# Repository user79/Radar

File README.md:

# Radar
This is a Frequency Modulated Continuous Wave (FMCW) ground penetrating radar (GPR) project aimed toward detection of land mines for humanitarian de-mining. It is based loosely on the online resources from MIT and U.C.Davis, as well as the presentation by Ferrara/Chizh/Pietrelli 2017.
* https://ocw.mit.edu/courses/res-ll-003-build-a-small-radar-system-capable-of-sensing-range-doppler-and-synthetic-aperture-radar-imaging-january-iap-2011/
* http://gpradar.eu/onewebmedia/TU1208_GPRforeducationaluse_November2017_FerraraChizhPietrelli.pdf
* https://github.com/ucdart/UCD-EEC134/
* http://dart.ece.ucdavis.edu/education/eec134.html
* http://dart.ece.ucdavis.edu/education/files/eec134-2017-2018/Team_DiodeHard3/AN_Yharo_Torres.pdf
* http://dart.ece.ucdavis.edu/education/files/eec134-2017-2018/Team_DeepSpaceAntenna/Team_DeepSpace_Antenna_Report.pdf

Here I have posted the circuit design, Eagle CAD schematic, and board layout for revision 1.

Unfortunately, in initial testing of this board with a sawtooth voltage input to produce a standard frequency sweep (and subsequent testing with discrete DC voltage inputs), the output voltage seems to be fluctuating according to some other pattern, not related to reflectors placed at varying distances from the antennas.  My initial guess is that there is a reflection (or set of reflections) from the board itself that is causing the mixing pattern, that is overshadowing any additional reflection mixing from the receive antenna.  There may be some coupling from the traces of the PCB.  The projects above used shielded coax cable to connect the various parts, and now I can see why.

Next, in summer 2023, I did some hardware testing with a different mixer (but using the same VCO from the original board). I was able to see radar action in tracking a person walking in a hallway, as shown. However, I was hitting some fundamental limits in resolution due to sampling rate and wavelength and other issues, as described in the "GPR progress summer2023.pdf" document.

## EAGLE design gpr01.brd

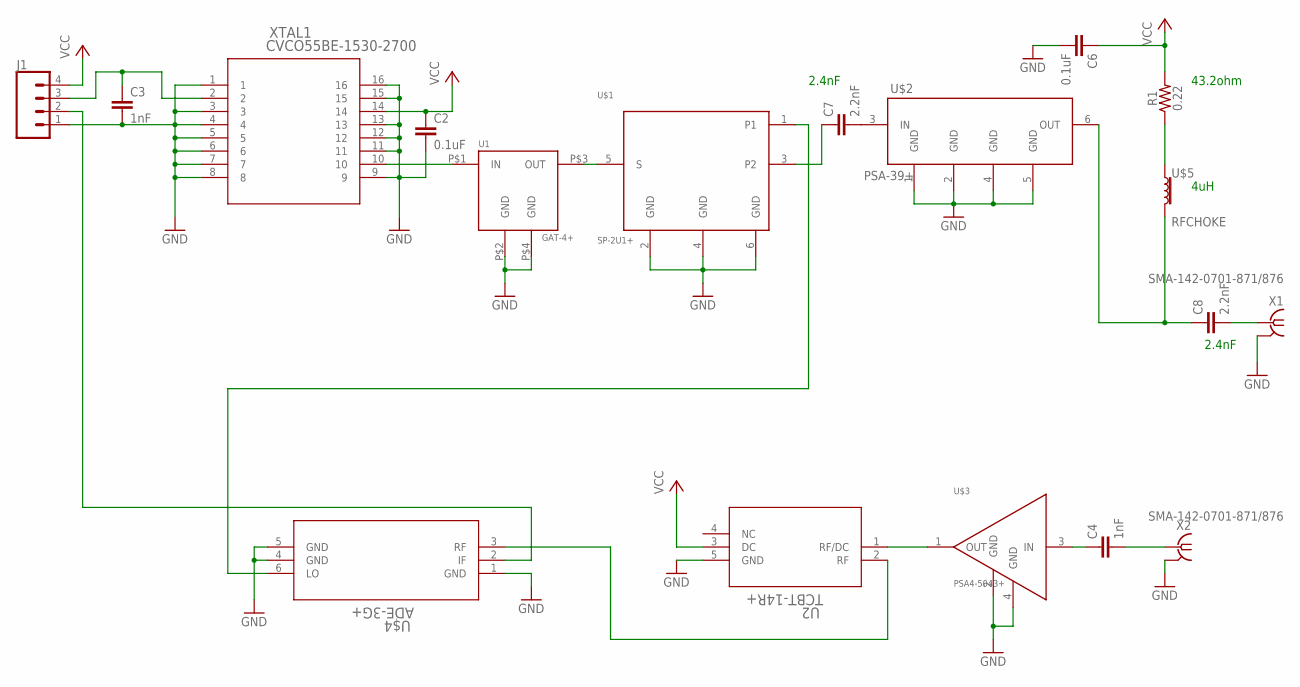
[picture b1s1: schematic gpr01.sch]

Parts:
C2, C6: 0.1uF; 0402
C3, C4: 1nF; 0603
C7, C8: 2.2nF; 0603
J1: CONN_04POLAR; MOLEX-1X4
R1: 0.22; 0805
U1: GAT-4+
U2: TCBT-14R+; GU1414-2_MNC
U$1: SP-2U1+; SOT23-6
U$2: PSA-39+; SOT363_PHILIPS
U$3: PSA4-5043+; SOT343
U$4: ADE-3G+; CD542_MNC
U$5: RFCHOKE; 1210
X1, X2: SMA-142-0701-871/876; J502-ND-142-0701-871/876
XTAL1: CVCO55BE-1530-2700; CVCO55BE-1530-2700_CRX

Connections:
GND: C2.2, C3.2, C6.2, J1.1, U1.P$2 (GND), U1.P$4 (GND), U2.5 (GND), U$1.2 (GND), U$1.4 (GND), U$1.6 (GND), U$2.1 (GND), U$2.2 (GND), U$2.4 (GND), U$2.5 (GND), U$3.2 (GND), U$3.4 (GND), U$4.1 (GND), U$4.4 (GND), U$4.5 (GND), X1.G@1 (2), X1.G@2 (2), X1.G@3 (2), X1.G@4 (2), X2.G@1 (2), X2.G@2 (2), X2.G@3 (2), X2.G@4 (2), XTAL1.1, XTAL1.3, XTAL1.4, XTAL1.5, XTAL1.6, XTAL1.7, XTAL1.8, XTAL1.9, XTAL1.11, XTAL1.12, XTAL1.13, XTAL1.15, XTAL1.16
unnamed: U1.P$1 (IN), XTAL1.10
unnamed: C3.1, J1.3, XTAL1.2
unnamed: U1.P$3 (OUT), U$1.5 (S)
unnamed: C7.1, U$1.3 (P2)
unnamed: C7.2, U$2.3 (IN)
unnamed: R1.1, U$5.1
unnamed: C8.1, U$2.6 (OUT), U$5.2
unnamed: C8.2, X1.1
unnamed: C4.2, X2.1
unnamed: C4.1, U$3.3 (IN)
unnamed: U2.1 (RF/DC), U$3.1 (OUT)
unnamed: U2.2 (RF), U$4.3 (RF)
unnamed: U$1.1, U$4.6 (LO)
unnamed: J1.2, U$4.2 (IF)
VCC: C2.1, C6.1, J1.4, R1.2, U2.3 (DC), XTAL1.14

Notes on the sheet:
2.4nF
43.2ohm
4uH

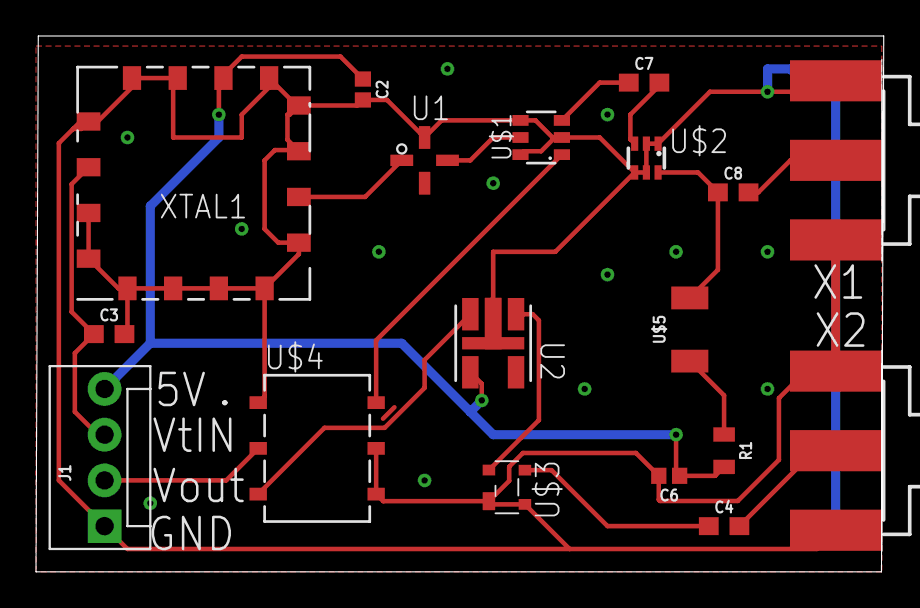
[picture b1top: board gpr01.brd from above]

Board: 2 copper layers, 47.1 x 29.8 mm, 18 parts (0 on the bottom side), 16 nets.

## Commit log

2022-07-29 Initial file upload of rev01. This revision shows mixing activity but it does not correspond to reflectors placed in front of antennas.
2025-12-02 posting updates from summer 2023

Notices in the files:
parts and their libraries:
SparkFun-Connectors: Licensing: Creative Commons ShareAlike 4.0 International - https://creativecommons.org/licenses/by-sa/4.0
COPYRIGHT: Copyright (C) 2018 Accelerated Designs. All rights reserved
